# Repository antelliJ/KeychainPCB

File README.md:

# Keychain
Creating a keychain PCB badge

## Purpose

This is a personalized PCB that aims to be carried around on a keychain, a fun PCB badge similar to the ones at opensauce. I hope this could be an interesting way to introduce myself in an interactive manner if I'm at any tech conferences or the like.

## Usage and Info

Uses either a CR2032 or USB-C to power a CH32V003 MCU, toggled between using a 2 way switch.

a LIS331HH communicates to the board to activate the LED's based on the motion associated.

Programmable input is available through the headers.

The back silkscreen plugs my [github account](https://github.com/antelliJ) through a link and a QR code

The front silkscreens include some random things I thought would be interesting, like a ruler and fun hints to get people interested in what the board can actually do

### File structure
`\PCB\` includes files relevant for the pcb and manufacturing. 
<br>
    `\PCB\production` are the files used for PCB manufacturing

`\Code\` is intended for all the code, which is basically empty at the moment. Eventually it will have the custom firmware.

### Features (mostly planned)
Shake to wake, various taps can cycle through the different animations.
One of which that would show a morse code representation of my name, among other small animations with the leds.

## Bill of Materials
A nicely formatted excel sheet is provided at `\PCB\production\Keychain-Bom.xlsx`
The below is just a static version of that...

| Designator                      | Footprint                            | Quantity | Price         | Value                         | JLCPCB Part #（optional） | MPN                                        | Links                                                                                                                                                              |
| ------------------------------- | ------------------------------------ | -------- | ------------- | ----------------------------- | ----------------------- | ------------------------------------------ | ------------------------------------------------------------------------------------------------------------------------------------------------------------------ |
| U2                              | LIS3DH breakout Board                | 1        |  $       3.15 | LIS3DH                        |                         | LIS3DHTR                                   | [https://www.aliexpress.com/item/1005010373628490.html](https://www.aliexpress.com/item/1005010373628490.html)                                                     |
| U4                              | TSSOP-20_4.4x6.5mm_P0.65mm           | 1        |  $       1.54 | CH32V003FxPx                  | C5187096                | CH32V003F4P6                               | [CH32V003F4P6 \| Microcontrollers \| WCH \| LCSC](https://www.lcsc.com/product-detail/C5187096.html)                                                               |
| U1                              | TO-252-3_TabPin2                     | 1        |  $       1.02 | AMS1117CD-3.3                 | C6186                   | AMS1117-3.3                                | [AMS1117-3.3 \| Voltage Regulators - Linear, Low Drop Out (LDO) Regulators \| Advanced Monolithic Systems \| LCSC](https://www.lcsc.com/product-detail/C6186.html) |
| D2                              | LED_RGB_1210                         | 1        |  $       0.68 | LED_RABG                      | C375572                 | E6C1209RGBC3UDA                            | [https://www.lcsc.com/product-detail/C375572.html](https://www.lcsc.com/product-detail/C375572.html)                                                               |
| R7                              | 0805                                 | 1        |  $       0.66 | 330 (RK led)                  | C17437                  | 0805W8F1200T5E                             | [https://www.lcsc.com/product-detail/C17437.html](https://www.lcsc.com/product-detail/C17437.html)                                                                 |
| C2, C4                          | 0805                                 | 2        |  $       0.63 | 10uF                          | C15850                  | CL21A106KAYNNNE                            | [https://www.lcsc.com/product-detail/C15850.html](https://www.lcsc.com/product-detail/C15850.html)                                                                 |
| J1                              | PinHeader_1x04_P2.54mm_Vertical      | 1        |  $       0.62 | Conn_01x04_Pin                | C52016392               | HX PH254-01-04-Z-L11.5 straight pin header | [https://www.lcsc.com/product-detail/C52016392.html](https://www.lcsc.com/product-detail/C52016392.html)                                                           |
| D1, D10, D3, D4, D5, D6, D8, D9 | 0805                                 | 8        |  $       0.62 | Red LED                       | C84256                  | NCD0805R1                                  | [https://www.lcsc.com/product-detail/C84256.html](https://www.lcsc.com/product-detail/C84256.html)                                                                 |
| R10, R11                        | 0805                                 | 2        |  $       0.55 | 5k1                           | C27834                  | 0805W8F5101T5E                             | [0805W8F5101T5E \| Chip Resistor - Surface Mount \| UNI-ROYAL \| LCSC](https://www.lcsc.com/product-detail/C27834.html)                                            |
| R1, R2, R3, R4                  | 0805                                 | 4        |  $       0.43 | 100                           | C17408                  | 0805W8F1000T5E                             | [0805W8F1000T5E \| Chip Resistor - Surface Mount \| UNI-ROYAL \| LCSC](https://www.lcsc.com/product-detail/C17408.html)                                            |
| SW1                             | SW-SMD_MST-12D18G4-SPDT-SLIDE-SWITCH | 1        |  $       0.40 | MST-12D18G4 SPDT SLIDE SWITCH | C49023767               | MST-12D18G4 SPDT Slide Switch              | [MST-12D18G4 SPDT Slide Switch \| Slide Switches \| SHOU HAN \| LCSC](https://www.lcsc.com/product-detail/C49023767.html)                                          |
| J2                              | USB_C_Receptacle_GCT_USB4085         | 1        |  $       0.38 | USB_C_Receptacle_PowerOnly_6P | C668623                 | TYPE-C 6P(073)                             | [https://www.lcsc.com/product-detail/C668623.html](https://www.lcsc.com/product-detail/C668623.html)                                                               |
| R12, R8, R9                     | 0805                                 | 3        |  $       0.30 | 4k7                           | C17673                  | 0805W8F4701T5E                             | [0805W8F4701T5E \| Chip Resistor - Surface Mount \| UNI-ROYAL \| LCSC](https://www.lcsc.com/product-detail/C17673.html)                                            |
| BT1                             | BatteryHolder_Keystone_1058_1x2032   | 1        |  $       0.30 | Battery_Cell                  | C5239862                | BS-02-A1AJ010                              | [https://www.lcsc.com/product-detail/C5239862.html](https://www.lcsc.com/product-detail/C5239862.html)                                                             |
| C1, C3                          | 0805                                 | 2        |  $       0.28 | 100nF                         | C49678                  | CC0805KRX7R9BB104                          | [https://www.lcsc.com/product-detail/C49678.html](https://www.lcsc.com/product-detail/C49678.html)                                                                 |
| BZ1                             | Buzzer_12x9.5RM7.6                   | 1        |  $       0.19 | Piezo buzzer (passive)        | C76871                  | PS1240P02BT                                | [https://www.lcsc.com/product-detail/C76871.html](https://www.lcsc.com/product-detail/C76871.html)                                                                 |
| Total for Components |  $11.75 | | | | | | |

** You may notice that r5 and r6 are missing, I included them in the schematic for the blue and green LEDs in the center RGB LED, but I don't think there is enough power for it to make it worth it? If anything it would just reduce the brightness from whatever it already is. Those pads should just be wired together if using the gerber files as is.

## References
A lot of things were picked up on the way of creating this project, with it being my first proper PCB

used [Spreadsheet to Markdown](https://tabletomarkdown.com/convert-spreadsheet-to-markdown/) to make the above BOM in the readme

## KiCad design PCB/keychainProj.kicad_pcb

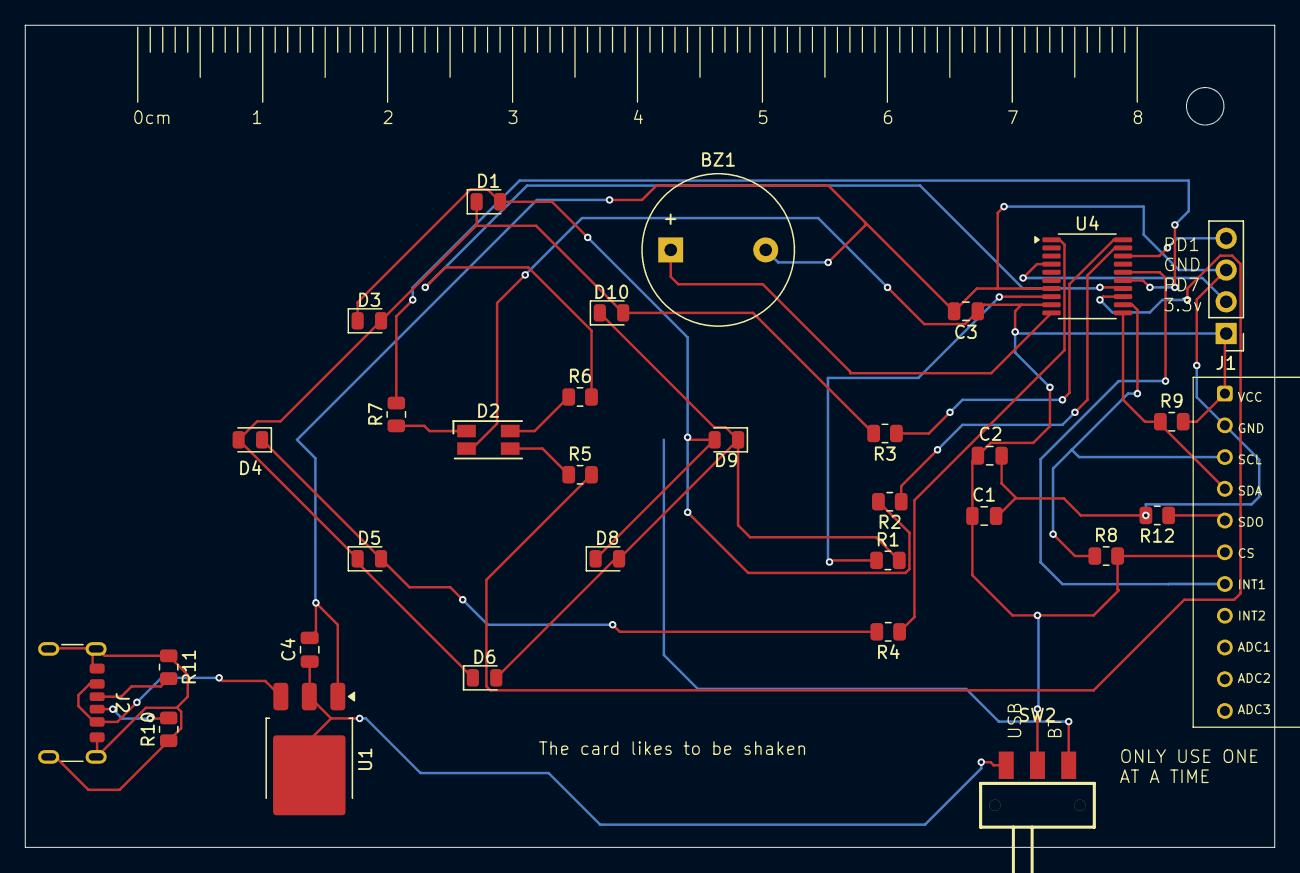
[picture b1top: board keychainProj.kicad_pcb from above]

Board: 2 copper layers, 100.0 x 65.8 mm, 34 parts (1 on the bottom side), 29 nets.

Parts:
BT1: Battery_Cell; BatteryHolder_Keystone_1058_1x2032
BZ1: Buzzer; Buzzer_12x9.5RM7.6
C1, C3: 100nF; C_0805_2012Metric
C2, C4: 10uF; C_0805_2012Metric
D1, D3, D4, D5, D6, D8, D9, D10: LED; LED_0805_2012Metric
D2: LED_RABG; LED_RGB_1210
H1: MountingHole; MountingHole_3mm
J1: Conn_01x04_Pin; PinHeader_1x04_P2.54mm_Vertical
J2: USB_C_Receptacle_PowerOnly_6P; USB_C_Receptacle_GCT_USB4125-xx-x-0190_6P_TopMnt_Horizontal
R1, R2, R3, R4: 100; R_0805_2012Metric
R5, R6: 0; R_0805_2012Metric
R7: 330; R_0805_2012Metric
R8, R9, R12: 4k7; R_0805_2012Metric
R10, R11: 5k1; R_0805_2012Metric
SW2: MST-12D18G4 SPDT SLIDE SWITCH; SW-SMD_MST-12D18G4-SPDT-SLIDE-SWITCH
U1: AMS1117CD-3.3; TO-252-3_TabPin2
U2: LIS3DH; LIS3DH_Aliexpress_Module
U4: CH32V003FxPx; TSSOP-20_4.4x6.5mm_P0.65mm

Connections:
+3.3V: C1.1, C2.1, C3.1, D2.2 (A), J1.1, R8.2, R9.2, SW2.2, U2.1 (VDD_IO), U2.8 (CS), U4.9 (VDD)
GND: BT1.2 (-), BZ1.2 (-), C1.2, C2.2, C3.2, C4.2, J1.3, R12.2, U1.1 (GND), U2.5 (GND), U4.7 (VSS)
unnamed: BT1.1 (+), SW2.3
unnamed: BZ1.1 (+), U4.10 (PC0)
unnamed: D1.2 (A), D3.1 (K), D8.1 (K), D9.2 (A), R2.2
unnamed: D1.1 (K), D3.2 (A), D4.2 (A), D5.1 (K), D6.1 (K), D10.2 (A), R3.2
unnamed: D2.3 (BK), R5.1
unnamed: D2.4 (GK), R6.1
unnamed: D2.1 (RK), R7.1
unnamed: D4.1 (K), D5.2 (A), R4.2
unnamed: D6.2 (A), D8.2 (A), D9.1 (K), D10.1 (K), R1.2
unnamed: J1.2, U4.4 (PD7)
unnamed: J1.4, U4.18 (PD1)
unnamed: J2.A5 (CC1), R11.2
unnamed: J2.B5 (CC2), R10.2
unnamed: J2.A12 (GND), J2.B12 (GND), J2.SH (SHIELD), R10.1, R11.1
unnamed: J2.A9 (VBUS), J2.B9 (VBUS), U1.3 (VI)
unnamed: C4.1, SW2.1, U1.2 (VO)
unnamed: U2.11 (INT1), U4.16 (PC6)
unnamed: R9.1, U2.6 (SDI), U4.11 (PC1)
unnamed: R12.1, U2.7 (SDO)
unnamed: R8.1, U2.4 (SPC), U4.12 (PC2)
unnamed: R5.2, U4.13 (PC3)
unnamed: R6.2, U4.14 (PC4)
unnamed: R7.2, U4.15 (PC5)
unnamed: R1.1, U4.8 (PD0)
unnamed: R2.1, U4.19 (PD2)
unnamed: R3.1, U4.20 (PD3)
unnamed: R4.1, U4.1 (PD4)

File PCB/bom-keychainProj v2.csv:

Reference,Qty,Value,Manufacturer,MPN,LCSC #,KiCad Footprint,LCSC Link,Notes
U4,1,CH32V003F4P6,WCH,CH32V003F4P6,C5187096,Package_SO:TSSOP-20_4.4x6.5mm_P0.65mm,https://www.lcsc.com/product-detail/C5187096.html,
U2,1,LIS3DH,ST,LIS3DHTR,C15134,Package_LGA:LGA-16_3x3mm_P0.5mm_LayoutBorder3x5y,https://www.lcsc.com/product-detail/C15134.html,
U1,1,AMS1117-3.3,Advanced Monolithic Systems,AMS1117-3.3,C6186,Package_TO_SOT_SMD:TO-252-3_TabPin2,https://www.lcsc.com/product-detail/C6186.html,Check package: footprint is TO-252 but this LCSC part is likely SOT-223
"D1,D3,D4,D5,D6,D8,D9,D10",8,Red LED,Kingbright,APT2012SURCK,C5875730,LED_SMD:LED_0805_2012Metric,https://www.lcsc.com/product-detail/C5875730.html,
D2,1,RGB LED (common anode),EKINGLUX,E6C1209RGBC3UDA,C375572,LED_SMD:LED_RGB_1210,https://www.lcsc.com/product-detail/Light-Emitting-Diodes-LE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,Check footprint size and pin order against datasheet
"R1,R2,R3,R4",4,100,FOJAN,FRC0603F1000TS,C2906981,Resistor_SMD:R_0805_2012Metric,https://www.lcsc.com/product-detail/C2906981.html,Part is 0603; footprint is 0805
"R5,R6",2,47,FOJAN,FRC0603F47R0TS,C2907043,Resistor_SMD:R_0805_2012Metric,https://www.lcsc.com/product-detail/C2907043.html,Part is 0603; footprint is 0805
R7,1,330,FH,TD03G3300BT,C666864,Resistor_SMD:R_0805_2012Metric,https://www.lcsc.com/product-detail/C666864.html,Confirm package matches footprint
"R8,R9",2,4.7k,YAGEO,RC0603FR-074K7L,C99782,Resistor_SMD:R_0805_2012Metric,https://www.lcsc.com/product-detail/C99782.html,Part is 0603; footprint is 0805
"R10,R11",2,5.1k,YAGEO,RC0603FR-075K1L,C105580,Resistor_SMD:R_0805_2012Metric,https://www.lcsc.com/product-detail/C105580.html,Part is 0603; footprint is 0805
R12,1,10k,YAGEO,RC0603FR-0710KL,C98220,Resistor_SMD:R_0805_2012Metric,https://www.lcsc.com/product-detail/C98220.html,Schematic value was 4k7; update to 10k. Part is 0603; footprint is 0805
"C1,C3",2,100nF,Samsung Electro-Mechanics,CL10B104KB8NNNC,C1591,Capacitor_SMD:C_0805_2012Metric,https://www.lcsc.com/product-detail/C1591.html,Part is 0603; footprint is 0805
"C2,C4",2,10uF,,,,Capacitor_SMD:C_0805_2012Metric,,No part chosen yet
BT1,1,CR2032 holder,MYOUNG,BS-02-A1AJ010,C5239862,Battery:BatteryHolder_Keystone_1058_1x2032,https://www.lcsc.com/product-detail/C5239862.html,Check footprint against this holder's datasheet
SW1,1,SPDT slide switch (ON-OFF-ON),C&K,JS203011AQN,C221667,Button_Switch_THT:SW_Slide_SPDT_Straight_CK_OS102011MS2Q,https://www.lcsc.com/product-detail/C221667.html,Footprint is for a different C&K series; check datasheet land pattern
J2,1,"USB-C receptacle, power only 6P",SHOU HAN,TYPE-C 6P(073),C668623,Connector_USB:USB_C_Receptacle_GCT_USB4085,https://www.lcsc.com/product-detail/C668623.html,Footprint is for a GCT 16-pin part; use this part's land pattern
BZ1,1,Piezo buzzer (passive),TDK,PS1240P02BT,C76871,Buzzer_Beeper:Buzzer_12x9.5RM7.6,https://www.lcsc.com/product-detail/C76871.html,Check lead spacing against datasheet
J1,1,"Header 1x4, 2.54 mm",,,,Connector_PinHeader_2.54mm:PinHeader_1x04_P2.54mm_Vertical,,No part chosen yet
